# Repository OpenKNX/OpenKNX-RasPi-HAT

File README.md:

# OpenKNX-RasPi-HAT

see https://github.com/OpenKNX/OpenKNX/wiki/OpenKNX-RasPi-HAT

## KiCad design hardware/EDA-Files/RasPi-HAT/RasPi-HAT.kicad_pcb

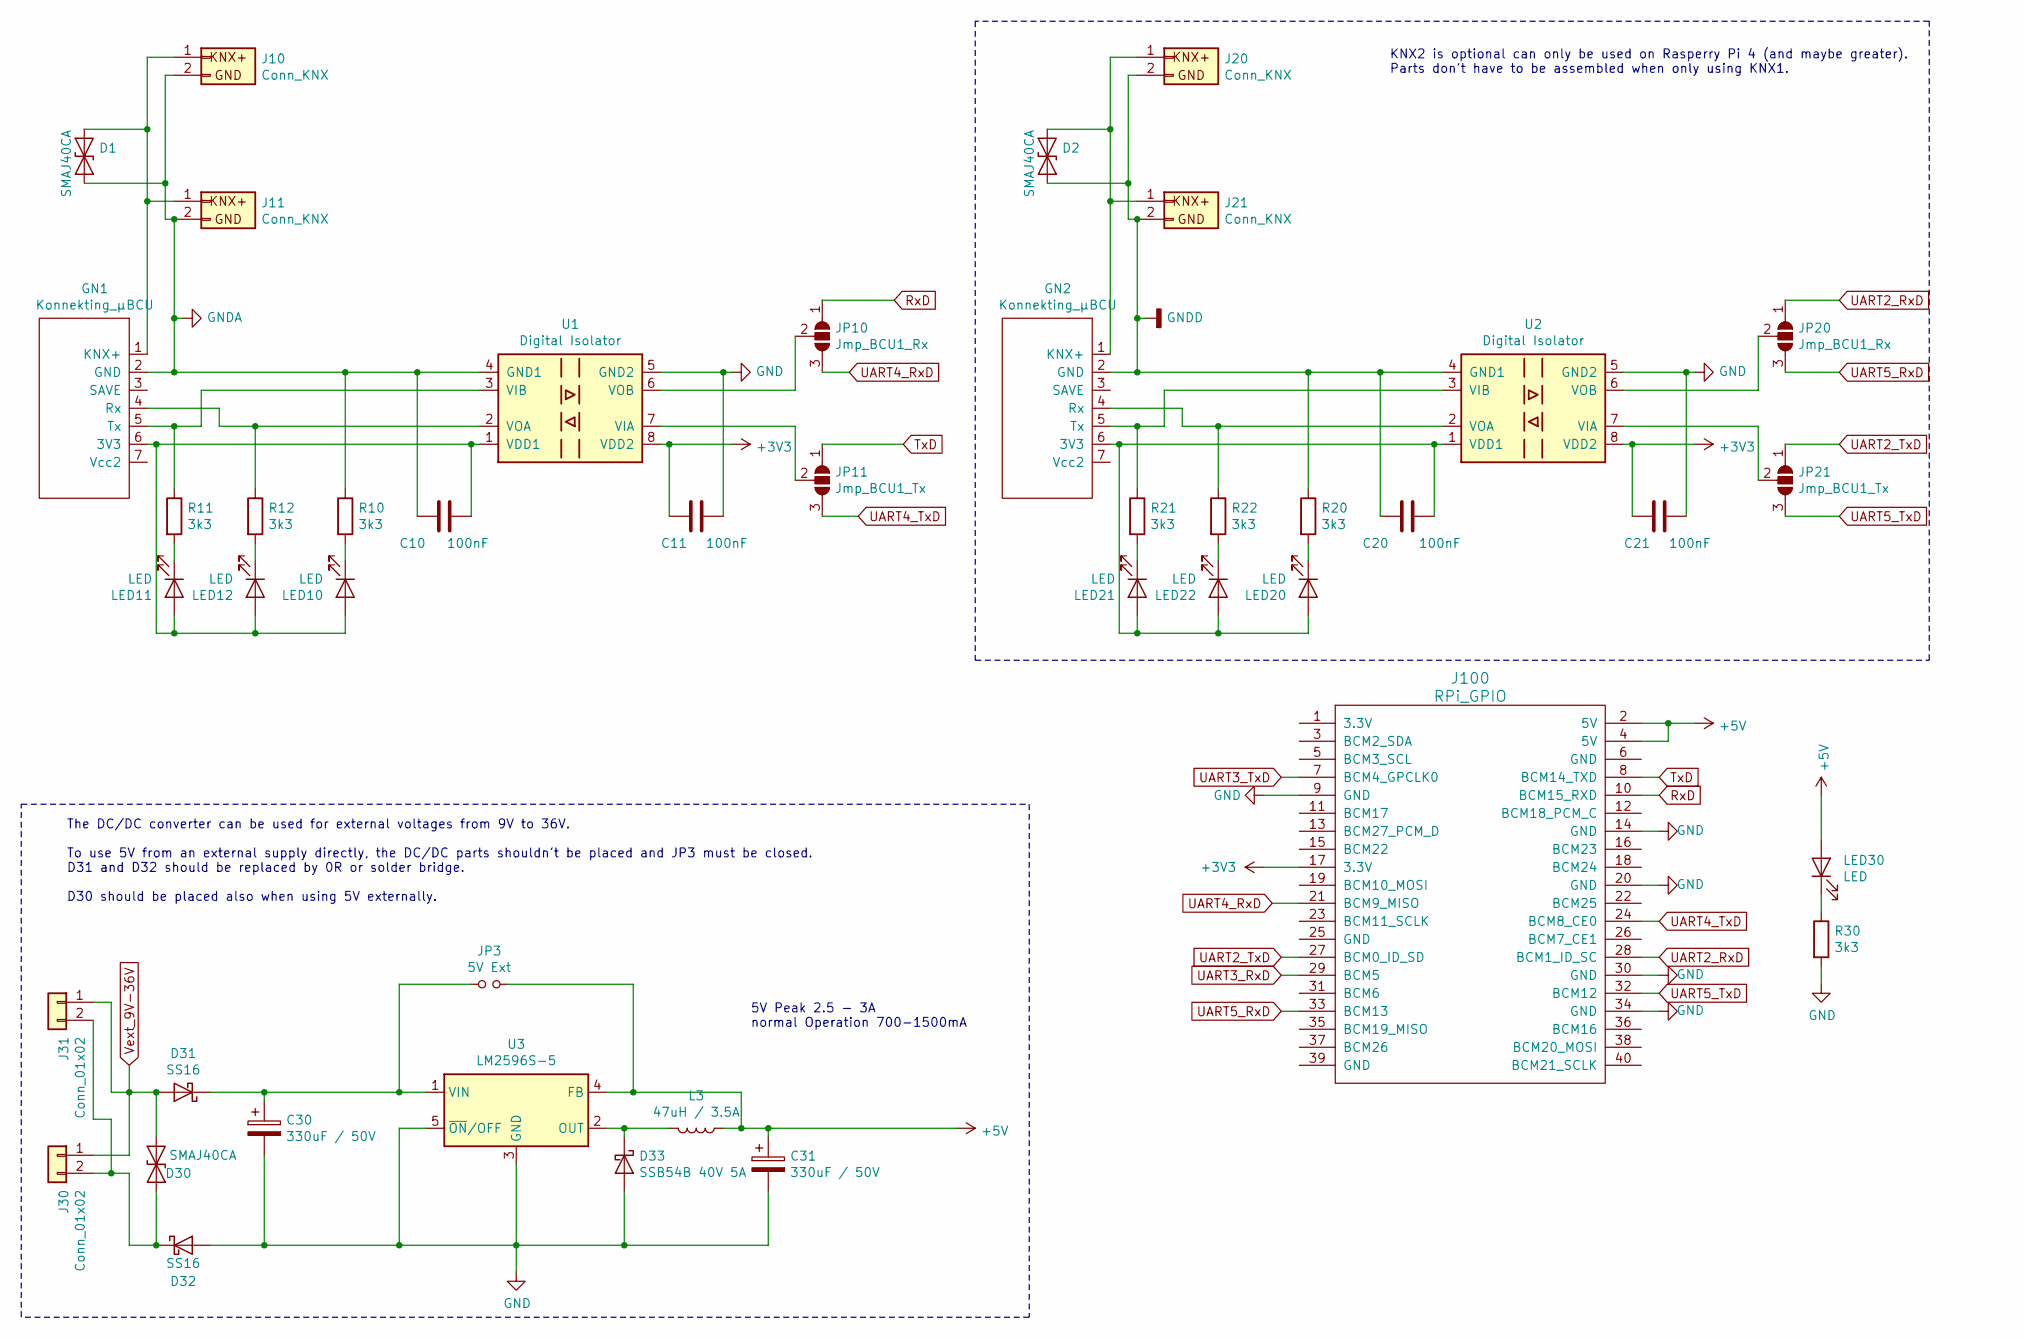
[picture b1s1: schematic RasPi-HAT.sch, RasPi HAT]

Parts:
C10, C11, C20, C21: 100nF; C_0603_1608Metric
C30, C31: 330uF / 50V; CP_Radial_D10.0mm_P5.00mm
D1, D2, D30: SMAJ40CA; D_SMA
D31, D32: SS16; D_SMA
D33: SSB54B 40V 5A; D_SMB
GN1, GN2: Konnekting_µBCU; MicroBCU2_PinHeader_SMD
J10, J20: Conn_KNX; KNX_Connector
J11, J21: Conn_KNX; PinHeader_1x02_P2.54mm_Vertical
J30: Conn_01x02; KNX_Connector
J31: Conn_01x02; PhoenixContact_MSTBA_2,5_2-G-5,08_1x02_P5.08mm_Horizontal
J100: RPi_GPIO; PinSocket_2x20_P2.54mm_Vertical
JP3: 5V Ext; PinHeader_1x02_P2.54mm_Vertical
JP10, JP20: Jmp_BCU1_Rx; SolderJumper-3_P1.3mm_Open_RoundedPad1.0x1.5mm
JP11, JP21: Jmp_BCU1_Tx; SolderJumper-3_P1.3mm_Open_RoundedPad1.0x1.5mm
L3: 47uH / 3.5A; L_YJYCOIN_YSPI1365_13.8mmx12.6mm_H6.5mm
LED10, LED11, LED12, LED20, LED21, LED22, LED30: LED; LED_0805_2012Metric_Castellated
R10, R11, R12, R20, R21, R22, R30: 3k3; R_0805_2012Metric_Pad1.15x1.40mm_HandSolder
U1, U2: Digital Isolator; SOIC-8_3.9x4.9mm_P1.27mm
U3: LM2596S-5; TO-263-5_TabPin3

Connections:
+3V3: C11.2, C21.2, J100.17 (3.3V), U1.8 (VDD2), U2.8 (VDD2)
+5V: C31.1, J100.2 (5V), J100.4 (5V), JP3.2, L3.1, LED30.2 (A), U3.4 (FB)
GND: C11.1, C21.1, C30.2, C31.2, D32.2 (A), D33.2 (A), J100.9 (GND), J100.14 (GND), J100.20 (GND), J100.30 (GND), J100.34 (GND), R30.2, U1.5 (GND2), U2.5 (GND2), U3.3 (GND), U3.5 (~ON~/OFF)
GNDA: C10.1, D1.2 (A2), GN1.2 (GND), J10.2, J11.2, R10.1, U1.4 (GND1)
GNDD: C20.1, D2.2 (A2), GN2.2 (GND), J20.2, J21.2, R20.1, U2.4 (GND1)
unnamed: C10.2, GN1.6 (3V3), LED10.2 (A), LED11.2 (A), LED12.2 (A), U1.1 (VDD1)
unnamed: C20.2, GN2.6 (3V3), LED20.2 (A), LED21.2 (A), LED22.2 (A), U2.1 (VDD1)
unnamed: C30.1, D31.1 (K), JP3.1, U3.1 (VIN)
unnamed: D1.1 (A1), GN1.1 (KNX+), J10.1, J11.1
unnamed: D2.1 (A1), GN2.1 (KNX+), J20.1, J21.1
unnamed: D30.1 (A1), D32.1 (K), J30.2, J31.2
unnamed: D33.1 (K), L3.2, U3.2 (OUT)
unnamed: GN1.4 (Rx), R12.1, U1.2 (VOA)
unnamed: GN1.5 (Tx), R11.1, U1.3 (VIB)
unnamed: GN2.4 (Rx), R22.1, U2.2 (VOA)
unnamed: GN2.5 (Tx), R21.1, U2.3 (VIB)
unnamed: JP10.2 (C), U1.6 (VOB)
unnamed: JP11.2 (C), U1.7 (VIA)
unnamed: JP20.2 (C), U2.6 (VOB)
unnamed: JP21.2 (C), U2.7 (VIA)
unnamed: LED10.1 (K), R10.2
unnamed: LED11.1 (K), R11.2
unnamed: LED12.1 (K), R12.2
unnamed: LED20.1 (K), R20.2
unnamed: LED21.1 (K), R21.2
unnamed: LED22.1 (K), R22.2
unnamed: LED30.1 (K), R30.1
RxD: J100.10 (BCM15_RXD), JP10.1 (A)
TxD: J100.8 (BCM14_TXD), JP11.1 (A)
UART2_RxD: J100.28 (BCM1_ID_SC), JP20.1 (A)
UART2_TxD: J100.27 (BCM0_ID_SD), JP21.1 (A)
UART3_RxD: J100.29 (BCM5)
UART3_TxD: J100.7 (BCM4_GPCLK0)
UART4_RxD: J100.21 (BCM9_MISO), JP10.3 (B)
UART4_TxD: J100.24 (BCM8_CE0), JP11.3 (B)
UART5_RxD: J100.33 (BCM13), JP20.3 (B)
UART5_TxD: J100.32 (BCM12), JP21.3 (B)
Vext_9V-36V: D30.2 (A2), D31.2 (A), J30.1, J31.1

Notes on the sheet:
The DC/DC converter can be used for external voltages from 9V to 36V. To use 5V from an external supply directly, the DC/DC parts shouldn't be placed and JP3 must be closed. D31 and D32 should be replaced by 0R or solder bridge. D30 should be placed also when using 5V externally.
5V Peak 2.5 - 3A normal Operation 700-1500mA
KNX2 is optional can only be used on Rasperry Pi 4 (and maybe greater). Parts don't have to be assembled when only using KNX1.

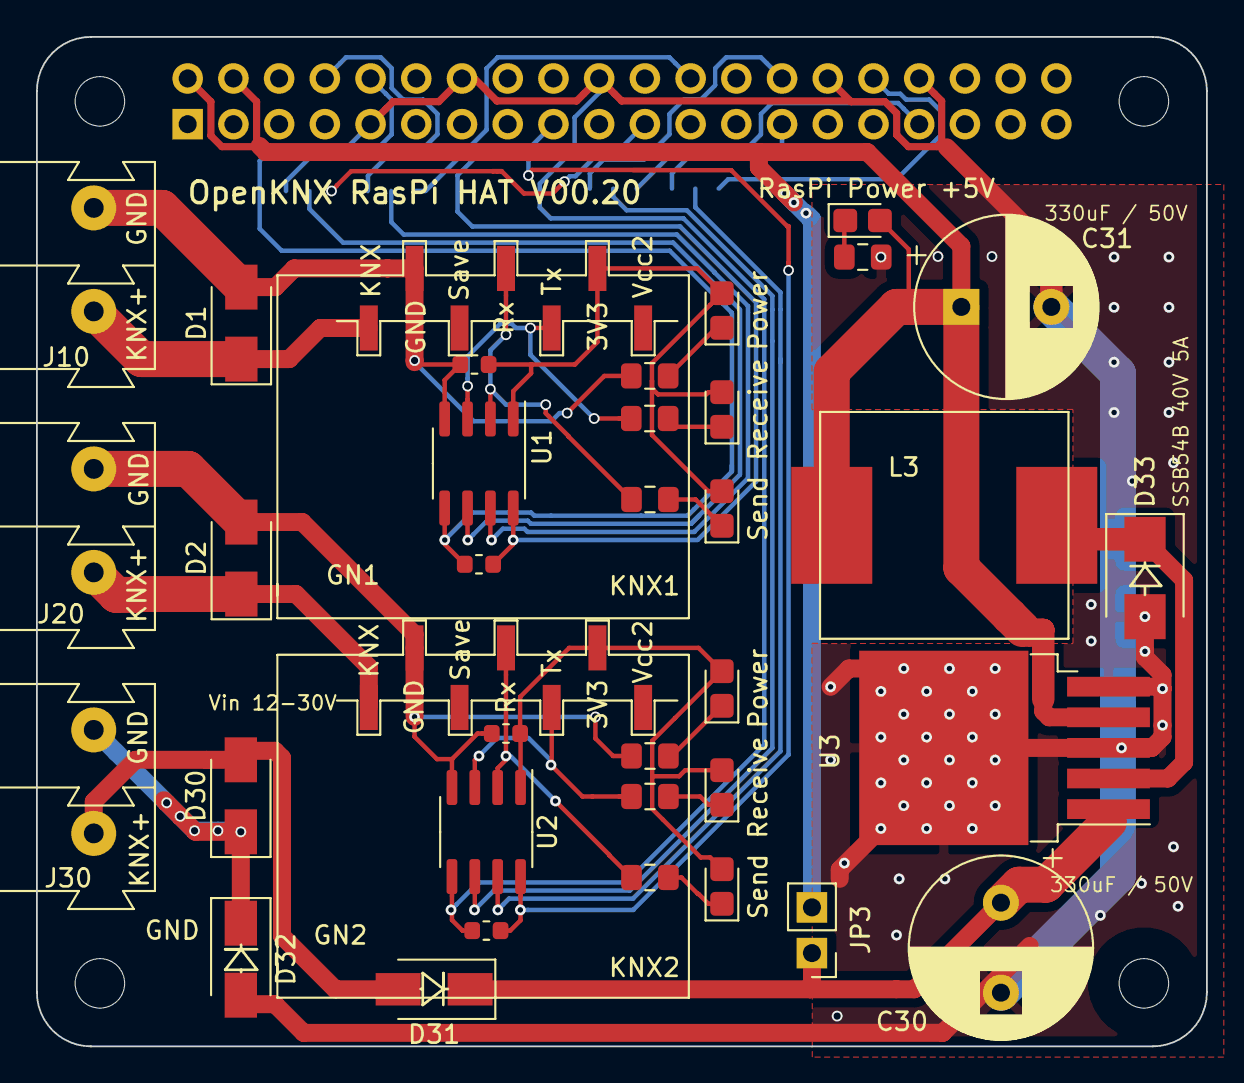
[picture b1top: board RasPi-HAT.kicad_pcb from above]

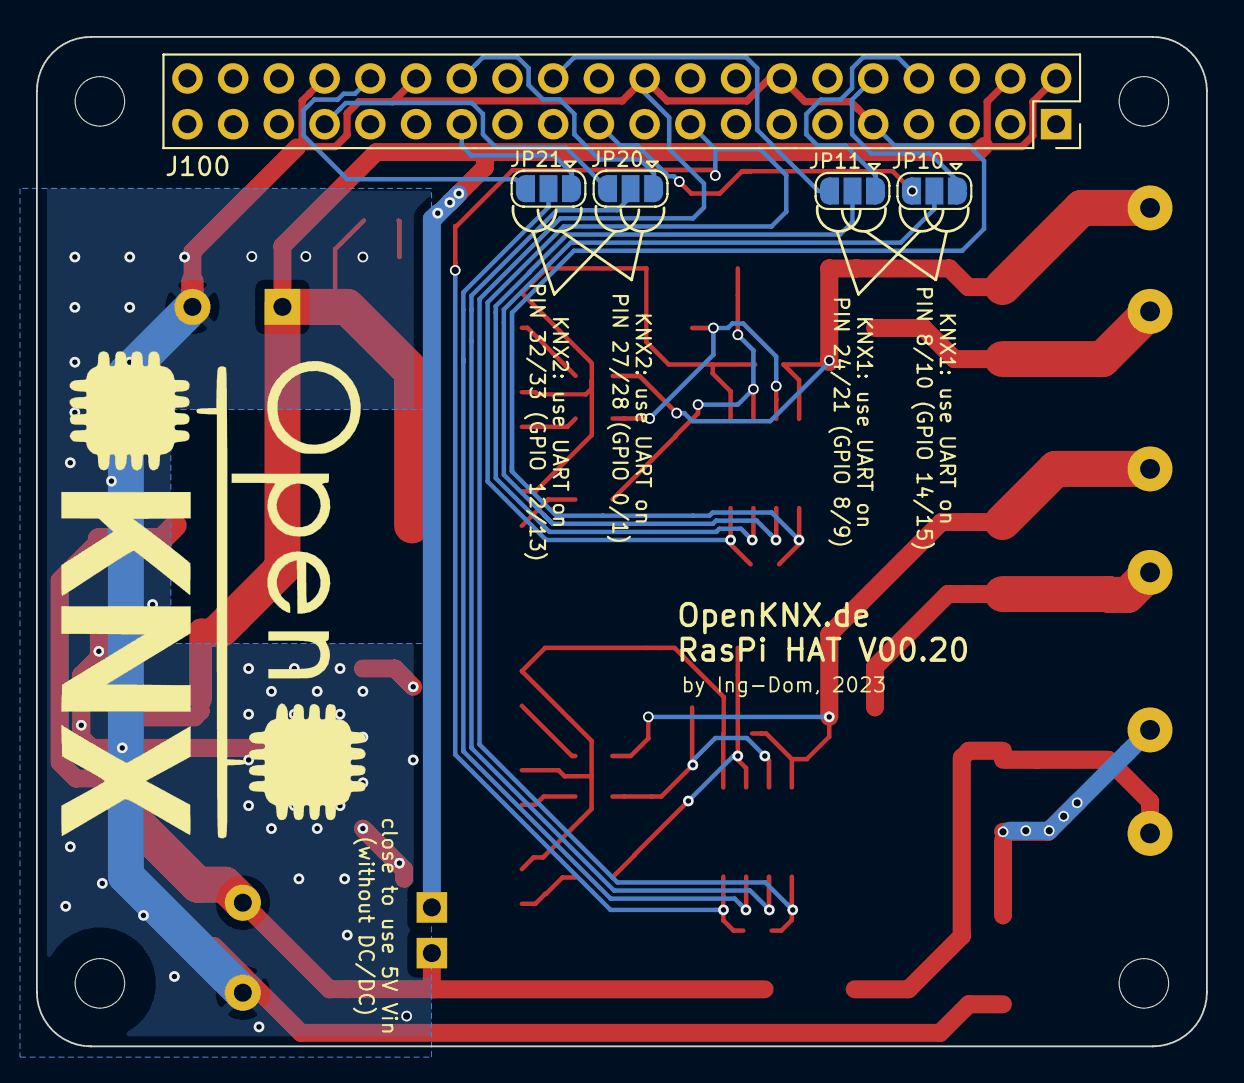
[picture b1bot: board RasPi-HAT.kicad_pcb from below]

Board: 2 copper layers, 65.0 x 56.1 mm, 41 parts (5 on the bottom side), 36 nets.

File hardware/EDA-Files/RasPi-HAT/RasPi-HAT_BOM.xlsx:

| Designator | Package | Designation | LCSC No | JLCPCB | Value | Cost | Alt value | LCSC No | JLCPCB
 | C10 | C_0603_1608Metric | 100nF | C14663 | basic | 100nF / 50V | 0.02
 | C11 | C_0603_1608Metric | 100nF | C14663 | basic | 100nF / 50V | 0.02
 | C20 | C_0603_1608Metric | 100nF | C14663 | basic | 100nF / 50V | 0.02
 | C21 | C_0603_1608Metric | 100nF | C14663 | basic | 100nF / 50V | 0.02
 | C30 | CP_Radial_D10.0mm_P5.00mm | 330uF / 50V | C160195 |  | 330uF / 50V | 0.18
 | C31 | CP_Radial_D10.0mm_P5.00mm | 330uF / 50V | C160195 |  | 330uF / 50V | 0.18
 | D1 | D_SMA_Handsoldering | SMAJ40CA | C113970 | extended |  | 0.04
 | D2 | D_SMA_Handsoldering | SMAJ40CA | C113970 | extended |  | 0.04
 | D30 | D_SMA_Handsoldering | SMAJ40CA | C113970 | extended |  | 0.04
 | D31 | D_SMA_Handsoldering | SS16 | C2481 | extended |  | 1.6E-2
 | D32 | D_SMA_Handsoldering | SS16 | C2481 | extended |  | 1.6E-2
 | D33 | D_SMB | SS54B 40V 5A | C32513 | extended |  | 7.1999999999999995E-2
 | GN1 | MicroBCU2_PinSocket | SMD Header 1x7 |  | ebay |  | 7.0000000000000007E-2
 | GN1 | MicroBCU2_PinSocket | Female Header 1x7 | C124418 | LCSC |  | 0.14000000000000001
 | GN2 | MicroBCU2_PinSocket | SMD Header 1x7 |  | ebay |  | 7.0000000000000007E-2
 | GN2 | MicroBCU2_PinSocket | Female Header 1x7 | C124418 | LCSC |  | 0.14000000000000001
 | J100 | PinSocket_2x20_P2.54mm_Vertical | RPi_GPIO | C50982 | LCSC |  | 0.18 |  | C35165 | LCSC
 | J10 | PhoenixContact_MSTBA_2,5_2-G-5,08_1x02_P5.08mm_Horizontal | Conn_KNX | C3697 | LCSC |  | 3.3000000000000002E-2
 | J10 | PhoenixContact_MSTBA_2,5_2-G-5,08_1x02_P5.08mm_Horizontal | Conn_KNX | C71370 | LCSC |  | 0.14799999999999999
 | J11 | PinHeader_1x02_P2.54mm_Vertical | Conn_KNX | C390678 | LCSC |  | 7.0000000000000001E-3
 | J20 | PhoenixContact_MSTBA_2,5_2-G-5,08_1x02_P5.08mm_Horizontal | Conn_KNX | C3697 | LCSC |  | 3.3000000000000002E-2
 | J20 | PhoenixContact_MSTBA_2,5_2-G-5,08_1x02_P5.08mm_Horizontal | Conn_KNX | C71370 | LCSC |  | 0.14799999999999999
 | J21 | PinHeader_1x02_P2.54mm_Vertical | Conn_KNX | C390678 | LCSC |  | 7.0000000000000001E-3
 | J30 | PhoenixContact_MSTBA_2,5_2-G-5,08_1x02_P5.08mm_Horizontal | Conn_01x02 | C3697 | LCSC |  | 3.3000000000000002E-2
 | J30 | PhoenixContact_MSTBA_2,5_2-G-5,08_1x02_P5.08mm_Horizontal | Conn_01x02 | C71370 | LCSC |  | 0.14799999999999999
 | JP3 | PinHeader_1x02_P2.54mm_Vertical | 5V Ext | C390678 | LCSC |  | 7.0000000000000001E-3
 | L3 | L_YJYCOIN_YSPI1365_13.8mmx12.6mm_H6.5mm | 47uH / 3.5A | C497913 | extended |  | 0.47 |  | C526031 | extended | C143967 | extended
 | LED10 | LED_0805_2012Metric_Castellated | LED | C84256 | basic |  | 0.02
 | LED11 | LED_0805_2012Metric_Castellated | LED | C84256 | basic |  | 0.02
 | LED12 | LED_0805_2012Metric_Castellated | LED | C84256 | basic |  | 0.02
 | LED20 | LED_0805_2012Metric_Castellated | LED | C84256 | basic |  | 0.02
 | LED21 | LED_0805_2012Metric_Castellated | LED | C84256 | basic |  | 0.02
 | LED22 | LED_0805_2012Metric_Castellated | LED | C84256 | basic |  | 0.02
 | LED30 | LED_0805_2012Metric_Castellated | LED | C84256 | basic |  | 0.02
 | R10 | R_0805_2012Metric_Pad1.15x1.40mm_HandSolder | 3k3 | C26010 | basic |  | 4.0000000000000001E-3
 | R11 | R_0805_2012Metric_Pad1.15x1.40mm_HandSolder | 3k3 | C26010 | basic |  | 4.0000000000000001E-3
 | R12 | R_0805_2012Metric_Pad1.15x1.40mm_HandSolder | 3k3 | C26010 | basic |  | 4.0000000000000001E-3
 | R20 | R_0805_2012Metric_Pad1.15x1.40mm_HandSolder | 3k3 | C26010 | basic |  | 4.0000000000000001E-3
 | R21 | R_0805_2012Metric_Pad1.15x1.40mm_HandSolder | 3k3 | C26010 | basic |  | 4.0000000000000001E-3
 | R22 | R_0805_2012Metric_Pad1.15x1.40mm_HandSolder | 3k3 | C26010 | basic |  | 4.0000000000000001E-3
 | R30 | R_0805_2012Metric_Pad1.15x1.40mm_HandSolder | 3k3 | C26010 | basic |  | 4.0000000000000001E-3
 | U1 | SOIC-8_3.9x4.9mm_P1.27mm | ADuM1201AR | C9669 | basic |  | 3.5 |  | C428879 | extended
 | U2 | SOIC-8_3.9x4.9mm_P1.27mm | ADuM1201AR | C9669 | basic |  | 3.5 |  | C428879 | extended
 | U3 | TO-263-5_TabPin3 | LM2596S-5 | C10002 | basic |  | 2.15 |  | C194349 | extended

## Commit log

2022-02-16 V00.04 and older
2022-06-21 added V00.10 schematic
2023-01-05 added stuff for RasPi-Case
2023-01-05 added pic
2023-01-25 added RasPi-Case V00.90
2023-01-25 added step
2024-01-14 pics
2024-07-27 release RasPi-HAT V00.20 KiCAD project
2024-07-27 add CC license
